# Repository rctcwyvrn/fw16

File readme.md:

# lily's framework 16 modules
Fun little projects

1. An FPGA expansion module
2. A tented, split keyboard on sleds that ride underneath the fw16

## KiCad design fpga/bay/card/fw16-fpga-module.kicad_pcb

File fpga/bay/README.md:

# bay

Expansion Bay work: `KEEPOUT.md` and `POWER.md` (Phase 2 section B), the rear-slot shell modification, and the custom AU15P card KiCad project under `card/` with its `BRINGUP.md`. Community interposer footprints are cloned into `lib/` (git-ignored) and must be pin-checked against the ExpansionBay Electrical README before use.

## FXBeam footprint check (2026-10-28)

Checked by script, pad by pad, against two Framework sources: the pin table in
`ExpansionBay/Electrical/README.md` (pin → signal → column/row) and the Neoconix drawing
`Dual-channel 74P FXBeam, length 27.75mm _Rev 2_` sheet 2, "Recommend DB footprint" (DWG FXBM-X148F027A).
Clones: FrameworkComputer/ExpansionBay `c9b8eef`, XPModder/Framework-ExpansionBay `2ec6368`,
jyancat/ExpansionBay `15efffe`. Framework's README says neither community footprint was tested by them.

Geometry from the drawing (origin at hole E, y up): pads 0.70 × 0.40 mm, column pitch 0.86 mm within a pair,
row pitch 0.60 mm (11 rows A–L, no I); power field on the left, signal field 16.65 mm to its right; columns
numbered 8 → 1 left to right in both fields; signal rows sit 0.25 mm above power rows. Holes: 2 × Ø2.70 NPTH
(interposer screws) with Ø4.50/Ø3.20 SMT rings on the back side, Ø1.50 NPTH × 4 and Ø1.40 NPTH × 2
(alignment). Solder-mask opening ≥ 0.5 × 0.8 mm per pad, i.e. ≥ 0.05 mm mask margin.

| | XPModder `Framework-FX-Beam` | jyancat `Expansion Bay FXBeam` |
| --- | --- | --- |
| Pad numbering | own geometric order (`P-1..74`, `D-1..74`), signal names carried by its symbol | row+column (`PA1`, `SL8`) |
| 148 pad positions | match the drawing | match the drawing |
| Pad → signal | **all 148 match** the README (after name normalisation: `…N`=`…#`, `SDA`=`DAT`) | **PJ6/PJ7/PJ8 are mis-named PJ1/PJ2/PJ3** — as shipped it shorts three GND pads to ID0, Fan1_SPEED and USB+ |
| NPTH diameters | match (drill 1.5 / 1.4 / 2.7; pad sizes 1.6 / 3.2 are mask openings) | match (1.5 / 1.4 / 2.7) |
| SMT rings | present, B.Cu, Ø4.5 pad over the 3.2 hole | **missing** |
| Mask margin | board default (must be ≥ 0.05) | board default (must be ≥ 0.05) |

XPModder's only gap is the mask margin; jyancat's naming bug makes it unsafe. Re-run with `bay/tools/fxbeam_check.py`. Pin-table facts the plan's step-1 list did not have: the power field also carries
**VSYS_GPU ×14** (7–20 V, "up to 10.5 A" on a high-power adapter, 15.2 V min on battery), **PWR_EN** (in, from
the PCH) and **PWR_GOOD** (out, power-sequencing sideband), plus EXT_SSD1/2_RST# and EXT_SSD2_CLK_REQ# for the
second PCIe port; the signal field has TH_OVERT# (PROCHOT#, drive low to throttle the system) and TH_ALERT#.
The "lane crossover" reported by the community was not found in either repo or the README; P/N pad order
does alternate between lanes (e.g. TX0 P below N, TX2 P above N), which is a layout matter, not a swap.

## How the EC powers the bay (research 2026-10-28)

From the FW16 ("lotus") EC source, `FrameworkComputer/EmbeddedController` branch `fwk-lotus-azalea-19573`,
`zephyr/program/framework/lotus/src/{gpu.c,gpu_configuration.c,power_sequence.c,adc.c}`, and
`FrameworkComputer/ExpansionBayConfigurationGenerator`. Not yet verified on hardware.

- **The bay is dead without two things on the card**, 5V_ALW and 3V3_ALW included ("ALW" is a misnomer):
  - ID0 and ID1 must read a valid ADC code (`gpu.c:127-183`): (12,12) = dual-interposer device, ≈2.135 V on
    the EC's 100 k pull-up. Inferred, medium confidence: **330 k to GND on each**, as Input Modules and
    XPModder's design use.
  - An EEPROM descriptor on I2C_*_ALW at 0x50 (or 0x52), magic `32 ac 00 00` + CRC32 + typed blocks
    (PCIE, FAN, VENDOR, GPIO). A blank EEPROM that ACKs falls back to the dual-SSD config. No EEPROM means
    nothing is enabled. XPModder uses a 24LC32.
  - The bay hatch/latch switch must also read closed.
- **The generator's "PCIe accessory" descriptor turns VSYS_GPU on from S3**, 3V/5V from S5, and GPIO0/1_EC high
  from S3. It sets `PCIE_8X1` and PCIE_MUX_SEL high. Write it with `framework_tool` or the EC `gpucfg`
  command. So VSYS_GPU *is* available to a non-GPU card.
- **Suspend:** VSYS stays live in S3/S0ix. The card must drop its own load on PERST# / D3.
- **PWR_EN** is driven by the APU (dGPU BOCO/D3cold) and only watched by the EC. Whether BIOS toggles it
  for an accessory is unknown, so PEX_RST# alone must be enough to gate the link. With PCIE_MUX_SEL high,
  **PWR_GOOD becomes the 2nd CLKREQ# and DP_A_AUX the 2nd REFCLK.**
- **Open:** whether PEX_TX/RX are named from the host or the module side (README marks PEX_TX as a module
  *input*; community thread t/75786 unresolved). Settle it from the GPU board PDFs on ExpansionBay branch
  `gpu_design` before S3. Also open: BIOS bifurcation for the accessory vendor, and Dual M.2 power tree.
  **PEX naming resolved 2026-10-29: host side** — see the next section.

## PEX_TX/RX direction (research 2026-10-29)

**PEX_TX/RX are named from the host side.** PEX_TXn is the laptop's transmitter and enters the card;
PEX_RXn is the card's transmitter. Confidence: medium-high (three independent sources agree, none is a
Framework schematic).

For the fpga sheet and the Path 3 XDC:

| Interposer net | Card end | AC coupling on the card |
| --- | --- | --- |
| PEX_TXn / PEX_TXn# | GTH **RX** (MGTHRXP/N) of lane n | none (the host's TX caps sit on the mainboard) |
| PEX_RXn / PEX_RXn# | GTH **TX** (MGTHTXP/N) of lane n | series cap, placed near the interposer |

Evidence:
- **The GPU board PDFs cannot answer it.** `Graphics Module Reference Design/AMD_7700S_GPU_Board.pdf` and
  `Nvidia_5070_GPU_Board.pdf` (6 sheets each) are mechanical drawings: part list, height zones, outline
  dimensions, FXBeam pad detail (sheet 4, Detail A) and paint lines. They show no components and no net
  names, so AC-cap placement is not visible. `Dual SSD Reference Design/fw_ssd_pcb_ref_design_0.pdf` is
  also mechanical; its sheet 1 has only a pin table.
- **Electrical README I/O column**, which is written from the module's side throughout (VSYS_GPU, Fan*_PWM,
  PWR_EN = I; Fan*_SPEED, PWR_GOOD, PEX_CLK_REQ# = O): PEX_TX0–7 = **I** (signal pins 2–24),
  PEX_RX0–7 = **O** (pins 26–48). The one row that breaks the convention is PEX_REFCLK = O (pins 50/51),
  which must be a typo, since the clock comes from the host.
- **XPModder's IO module** (`XPModder/Framework-ExpansionBay`, `ExpansionBay ExtensionCard
  Module/Framework-ExpansionBay-IO-Module/usb3.kicad_sch`, re-cloned 2026-10-29 at HEAD): PEX_TX0± goes
  straight to the uPD720201's **PERXP/PERXN** (receive, pins 10/11). PEX_RX0± goes through 100 nF caps
  C1/C2 to its transmitter. Traced by wire connectivity, not by eye. Whether that board was built and
  works is unknown.
- **Community thread t/75786 "PCIe data lines":** Filip reports that the M.2 reference board wires interposer
  RX to M.2 RX and TX to TX. M.2 pin names (PETp0 / PERp0) are host-side, so this matches. One community
  report, not from Framework staff.

Consequence: the card puts PCIe Gen4 AC caps (base spec 176–265 nF, i.e. 220 nF 0201/0402) on PEX_RX0–3
only. XPModder's 100 nF suits its Gen2 controller, not Gen4. A TX/RX swap cannot be fixed by lane
polarity inversion, so S3 must keep this mapping.

## Reference PCB vs README (2026-10-28)

`PCB Reference Design/FW_EXPANSION_BAY_PCB_0807.pdf` sheet 2 has its own pin definition table. It agrees with
the Electrical README on every pad except three in the power field: 3PF / 3PG / 2PG are **I2C_CLK_VS /
I2C_DAT_VS / I2C_INT_VS** there, but **EXT_SSD1_RST# / EXT_SSD2_RST# / EXT_SSD2_CLK_REQ#** in the README. The
README is newer (Dual-SSD era), so we follow it; these pads only go to test pads anyway. The same sheet gives
the shell's fan connector: **AFC58-S04FIA-R1 × 2**, pin 1 +12V, 2 FANx_SPEED, 3 FANx_PWM, 4 GND.

## XCAU15P-FFVB676 package facts (2026-10-28)

- **Height:** lidded flip-chip. A (seated, balls included) = 3.12 / 3.31 / 3.52 mm min/nom/max; lid ≤ 22.10 mm
  square on a 27 × 27 mm body; 1.0 mm pitch, 26 × 26. UG575 v1.22 Fig 4-10 (p. 454).
- **Transceivers:** all 12 GTH (Quads 224, 225, 226) sit on the **column 1–7 edge** (the pin-1 side in top
  view): Quad 226 rows F–L, Quad 225 rows M–W, Quad 224 rows Y–AF. UG575 Fig 3-83 (p. 311, top view).
- **PCIe:** a single hard block, PCIE4C_X0Y0 (Gen4 up to x4). Lane-0 quad options per PG213 v1.3 Table 94:
  GTH_Quad_224 (x4), GTH_Quad_225 (x8). REFCLK goes to GTREFCLK0 of the lane-0 quad.

## AFC58-S04FIA-R1 fan connector footprint (research 2026-10-29)

Source: `PCB Reference Design/Datasheets/J200_J201-SP010036Q00_LTCX00A2N00_AFC58-S04FIA-R1.pdf` in the
`gpu_design` clone. Page 1 is the Hefeng customer drawing for the whole AFC58-S series, 0.5 mm pitch,
H = 1.5 mm, FPC/FFC "Easy-on" right-angle SMT, rev A 2020-09-11. Page 2 is the tape and reel. The drawing
is generic, so the CKTS = 4 row of its table applies. Part-number decode (note 4): 04 circuits, **F = lower
contacts**, I = gold flash, A = tape and reel, R1 = natural housing with a black latch. A web search on
2026-10-29 found no LCSC/JLCPCB listing under this number (LCSC itself not queried directly), so plan for
consignment or hand placement.

**Verify before creating the footprint.** The page is a raster image. It could only be read at thumbnail
resolution here, because `pdftoppm`, `pdftocairo` and `pdfimages` needed approval that a headless run
could not get. Rows marked **(low-res)** need a check against a zoomed render.

| Item | Value | Drawing callout |
| --- | --- | --- |
| Signal pads | 4, numbered 1–4 from the "Circuit 1" end | "Recommended P.C.B pattern layout" |
| Pad pitch | 0.50 ± 0.05 mm | pattern, top-left |
| Signal pad width | 0.30 ± 0.05 mm | pattern, top-right |
| Signal pad length | 1.10 ± 0.05 mm **(low-res)** | pattern, right vertical callout |
| Pad 1 → pad 4 centre span | DIM A = 1.50 ± 0.05 mm | pattern "DIM A", table CKTS 4 |
| Fitting-nail pads | 2, mechanical (unnumbered, or "MP") | pattern, both ends |
| Nail pad size | 1.00 ± 0.05 (X) × 1.60 ± 0.05 (Y) mm **(low-res)** | pattern, bottom-left |
| Nail pad inner edge → pad 1 centre (X) | 1.60 ± 0.05 mm **(low-res)**. Working reading: nail centres at X = ±2.85 mm from the connector centre, giving an outer copper span of 6.70 mm. | pattern, bottom "1.60 ± 0.05". The "(0.15)" reference by Circuit 1 suggests the callout ends on the pad centreline. |
| Signal row → nail pads (Y) | 2.00 ± 0.05 mm **(low-res)**. Unclear whether it runs from the signal-pad outer edge to the nail-pad near edge or to the far edge. | pattern, right "2.00 ± 0.05" |
| Housing width | DIM A + 2.56 = 4.06 mm | top view |
| Overall width incl. nails | DIM B = 6.40 ± 0.15 mm | front view, table |
| DIM C / DIM D | 2.60 ± 0.05 / 5.40 ± 0.10 mm | front view, table |
| Depth | 3.83 mm body; 4.45 mm overall; terminal tail 1.10 mm | side view |
| Height | 1.50 mm (datum Z); latch opens to 105° | side view, section A-A |
| Mating FPC | 0.30 ± 0.03 mm thick, 2.50 ± 0.08 mm wide (DIM A + 1.00), conductors 0.30 ± 0.03 mm on 0.50 pitch, ≥ 2.70 mm exposed, ≥ 3.5 mm stiffener | "Recommended FPC/FFC dimension" |

Sanity check: the 6.70 mm working-reading pad span is wider than the 6.40 mm part (nail pads overhanging the
nails), which is how such land patterns usually look. The other reading, 1.60 mm nail-centre to pad-1-centre,
gives a 5.70 mm span, narrower than the part, which is unlikely. Pinout (FW_EXPANSION_BAY_PCB_0807.pdf
sheet 2): 1 +12V_FAN, 2 FANx_SPEED, 3 FANx_PWM, 4 GND. **Open:** which side of the fan FPC has its contacts
exposed. A lower-contact connector needs the conductors facing the board. The UMA fan spec PDFs have no
extractable text.

**Verified 2026-10-29 against a 300 dpi render, and built as `fw16-fpga-module:AFC58-S04FIA-R1`.** The low-res rows hold.
The 2.00 mm callout runs from the signal-pad edge nearest the nails to the far edge of the nail pad. The
top view's 3.10 mm (terminal tip to the nail edge) equals 1.10 + 2.00, and the nail metal sits 1.93–3.10 mm behind
the terminal tip. The pad-1 centre is 1.60 mm from the nail pad's inner edge.

Footprint frame: origin at the signal-pad centre. Pads 1–4 are 0.30 × 1.10 mm at x = −0.75…+0.75, y = 0. The two `MP`
nail pads are 1.00 × 1.60 mm at x = ±2.85, y = +1.75. The terminal tip is at y −0.70, and the housing runs to y +3.75.
The courtyard is ±3.6 × (−0.95…+4.0). The MP pads have no net, because the symbol is a plain `Conn_01x04`. Tie them
to GND in the PCB if the reference board does. The connectors go on the **bottom** side (CAD), so flip them at
placement.

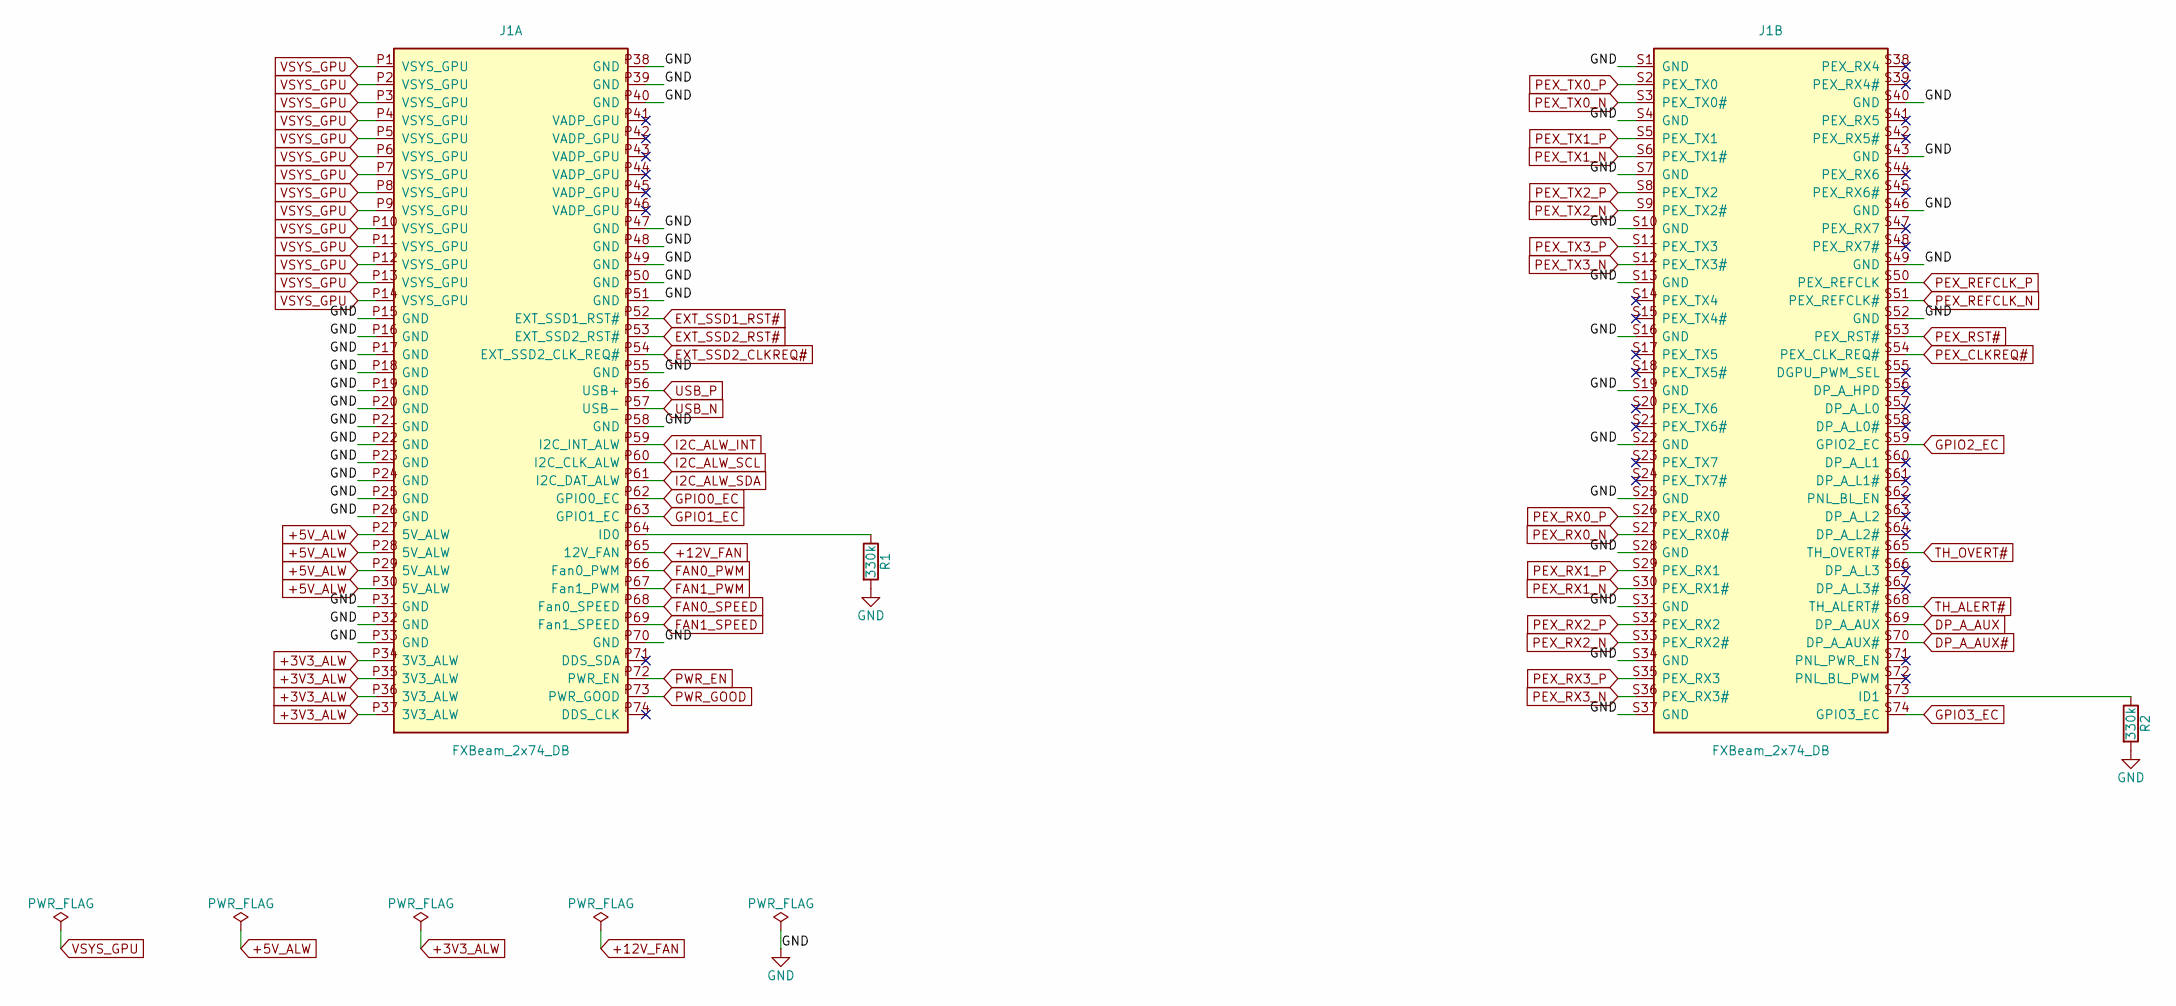
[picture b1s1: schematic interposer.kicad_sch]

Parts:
J1: FXBeam_2x74_DB
R1, R2: 330k; R_0402_1005Metric

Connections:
+3V3_ALW: J1.P34 (3V3_ALW), J1.P35 (3V3_ALW), J1.P36 (3V3_ALW), J1.P37 (3V3_ALW); also elsewhere on the board
+5V_ALW: J1.P27 (5V_ALW), J1.P28 (5V_ALW), J1.P29 (5V_ALW), J1.P30 (5V_ALW); also elsewhere on the board
+12V_FAN: J1.P65 (12V_FAN); also elsewhere on the board
DP_A_AUX: J1.S69 (DP_A_AUX); also elsewhere on the board
DP_A_AUX#: J1.S70 (DP_A_AUX#); also elsewhere on the board
EXT_SSD1_RST#: J1.P52 (EXT_SSD1_RST#); also elsewhere on the board
EXT_SSD2_CLKREQ#: J1.P54 (EXT_SSD2_CLK_REQ#); also elsewhere on the board
EXT_SSD2_RST#: J1.P53 (EXT_SSD2_RST#); also elsewhere on the board
FAN0_PWM: J1.P66 (Fan0_PWM); also elsewhere on the board
FAN0_SPEED: J1.P68 (Fan0_SPEED); also elsewhere on the board
FAN1_PWM: J1.P67 (Fan1_PWM); also elsewhere on the board
FAN1_SPEED: J1.P69 (Fan1_SPEED); also elsewhere on the board
GND: J1.P15 (GND), J1.P16 (GND), J1.P17 (GND), J1.P18 (GND), J1.P19 (GND), J1.P20 (GND), J1.P21 (GND), J1.P22 (GND), J1.P23 (GND), J1.P24 (GND), J1.P25 (GND), J1.P26 (GND), J1.P31 (GND), J1.P32 (GND), J1.P33 (GND), J1.P38 (GND), J1.P39 (GND), J1.P40 (GND), J1.P47 (GND), J1.P48 (GND), J1.P49 (GND), J1.P50 (GND), J1.P51 (GND), J1.P55 (GND), J1.P58 (GND), J1.P70 (GND), J1.S1 (GND), J1.S4 (GND), J1.S7 (GND), J1.S10 (GND), J1.S13 (GND), J1.S16 (GND), J1.S19 (GND), J1.S22 (GND), J1.S25 (GND), J1.S28 (GND), J1.S31 (GND), J1.S34 (GND), J1.S37 (GND), J1.S40 (GND), J1.S43 (GND), J1.S46 (GND), J1.S49 (GND), J1.S52 (GND), R1.2, R2.2; also elsewhere on the board
GPIO0_EC: J1.P62 (GPIO0_EC); also elsewhere on the board
GPIO1_EC: J1.P63 (GPIO1_EC); also elsewhere on the board
GPIO2_EC: J1.S59 (GPIO2_EC); also elsewhere on the board
GPIO3_EC: J1.S74 (GPIO3_EC); also elsewhere on the board
I2C_ALW_INT: J1.P59 (I2C_INT_ALW); also elsewhere on the board
I2C_ALW_SCL: J1.P60 (I2C_CLK_ALW); also elsewhere on the board
I2C_ALW_SDA: J1.P61 (I2C_DAT_ALW); also elsewhere on the board
unnamed: J1.P64 (ID0), R1.1
unnamed: J1.S73 (ID1), R2.1
PEX_CLKREQ#: J1.S54 (PEX_CLK_REQ#); also elsewhere on the board
PEX_REFCLK_N: J1.S51 (PEX_REFCLK#); also elsewhere on the board
PEX_REFCLK_P: J1.S50 (PEX_REFCLK); also elsewhere on the board
PEX_RST#: J1.S53 (PEX_RST#); also elsewhere on the board
PEX_RX0_N: J1.S27 (PEX_RX0#); also elsewhere on the board
PEX_RX0_P: J1.S26 (PEX_RX0); also elsewhere on the board
PEX_RX1_N: J1.S30 (PEX_RX1#); also elsewhere on the board
PEX_RX1_P: J1.S29 (PEX_RX1); also elsewhere on the board
PEX_RX2_N: J1.S33 (PEX_RX2#); also elsewhere on the board
PEX_RX2_P: J1.S32 (PEX_RX2); also elsewhere on the board
PEX_RX3_N: J1.S36 (PEX_RX3#); also elsewhere on the board
PEX_RX3_P: J1.S35 (PEX_RX3); also elsewhere on the board
PEX_TX0_N: J1.S3 (PEX_TX0#); also elsewhere on the board
PEX_TX0_P: J1.S2 (PEX_TX0); also elsewhere on the board
PEX_TX1_N: J1.S6 (PEX_TX1#); also elsewhere on the board
PEX_TX1_P: J1.S5 (PEX_TX1); also elsewhere on the board
PEX_TX2_N: J1.S9 (PEX_TX2#); also elsewhere on the board
PEX_TX2_P: J1.S8 (PEX_TX2); also elsewhere on the board
PEX_TX3_N: J1.S12 (PEX_TX3#); also elsewhere on the board
PEX_TX3_P: J1.S11 (PEX_TX3); also elsewhere on the board
PWR_EN: J1.P72 (PWR_EN); also elsewhere on the board
PWR_GOOD: J1.P73 (PWR_GOOD); also elsewhere on the board
TH_ALERT#: J1.S68 (TH_ALERT#); also elsewhere on the board
TH_OVERT#: J1.S65 (TH_OVERT#); also elsewhere on the board
USB_N: J1.P57 (USB-); also elsewhere on the board
USB_P: J1.P56 (USB+); also elsewhere on the board
VSYS_GPU: J1.P1 (VSYS_GPU), J1.P2 (VSYS_GPU), J1.P3 (VSYS_GPU), J1.P4 (VSYS_GPU), J1.P5 (VSYS_GPU), J1.P6 (VSYS_GPU), J1.P7 (VSYS_GPU), J1.P8 (VSYS_GPU), J1.P9 (VSYS_GPU), J1.P10 (VSYS_GPU), J1.P11 (VSYS_GPU), J1.P12 (VSYS_GPU), J1.P13 (VSYS_GPU), J1.P14 (VSYS_GPU); also elsewhere on the board

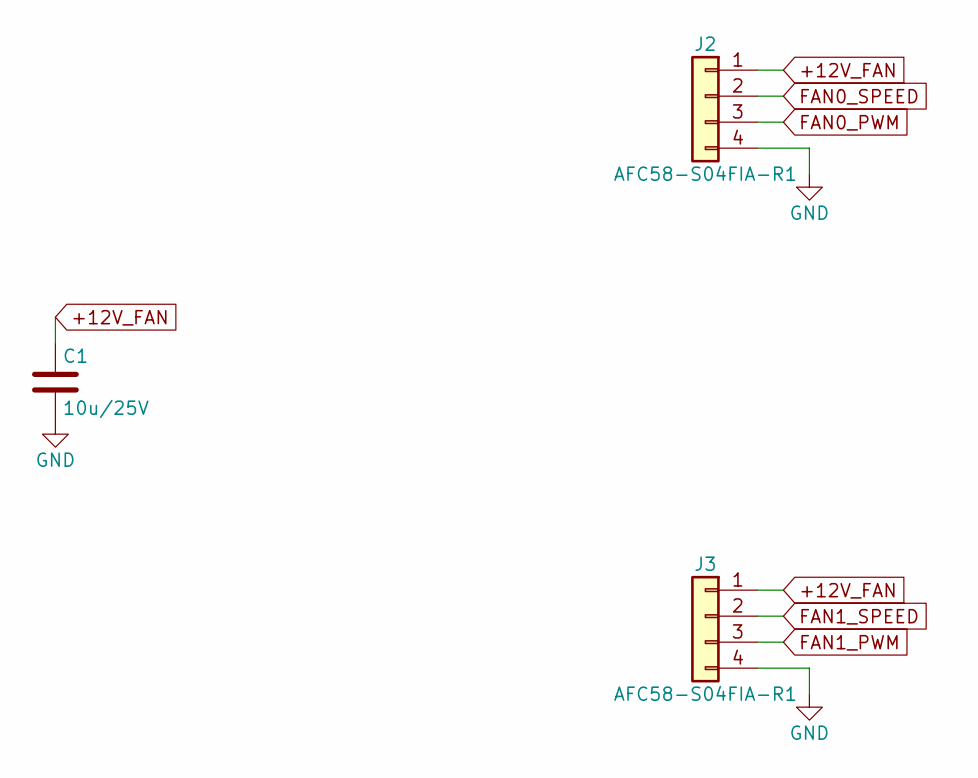
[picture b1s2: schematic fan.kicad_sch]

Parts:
C1: 10u/25V; C_1206_3216Metric
J2, J3: AFC58-S04FIA-R1

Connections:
+12V_FAN: C1.1, J2.1, J3.1; also elsewhere on the board
FAN0_PWM: J2.3; also elsewhere on the board
FAN0_SPEED: J2.2; also elsewhere on the board
FAN1_PWM: J3.3; also elsewhere on the board
FAN1_SPEED: J3.2; also elsewhere on the board
GND: C1.2, J2.4, J3.4; also elsewhere on the board

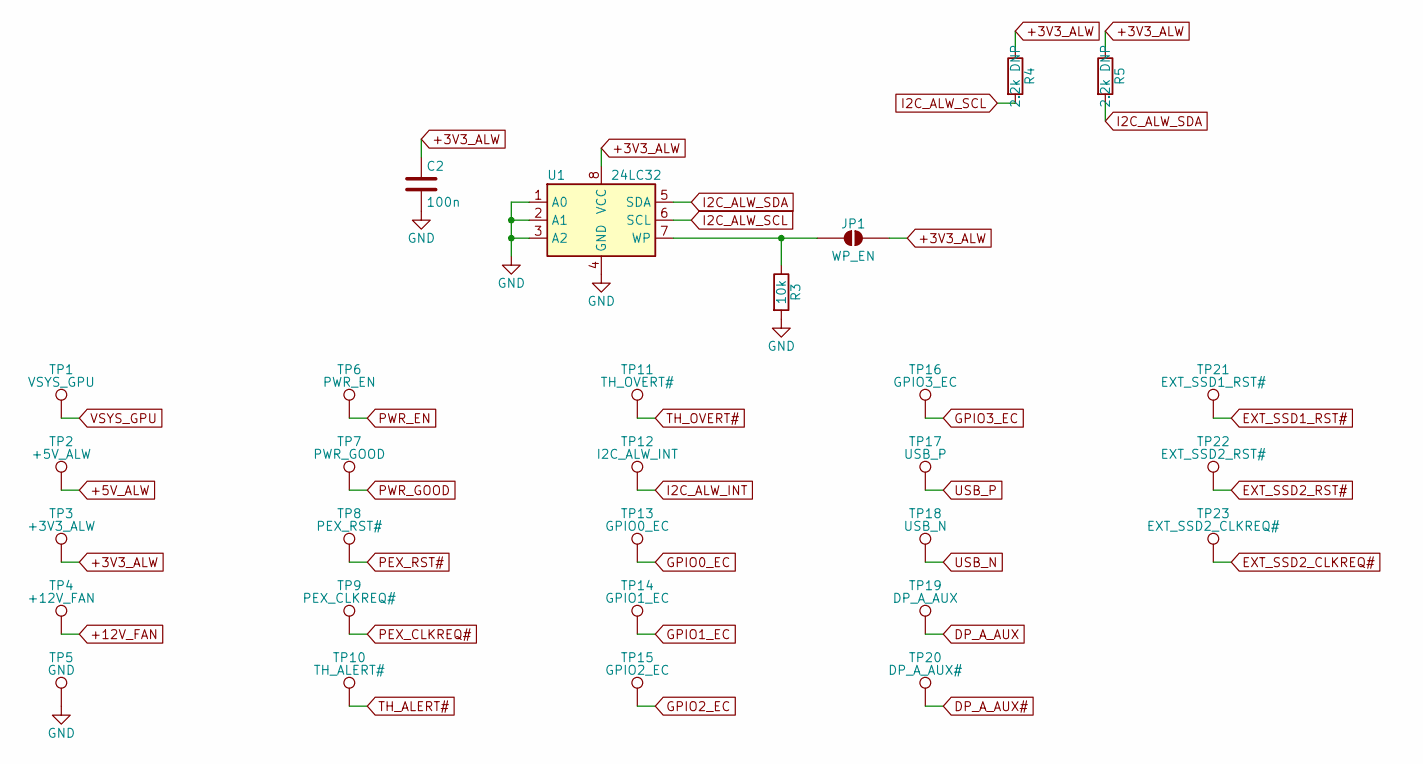
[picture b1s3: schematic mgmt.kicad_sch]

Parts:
C2: 100n; C_0402_1005Metric
JP1: WP_EN; SolderJumper-2_P1.3mm_Open_Pad1.0x1.5mm
R3: 10k; R_0402_1005Metric
R4, R5: 2.2k DNP; R_0402_1005Metric
TP1: VSYS_GPU; TestPoint_Pad_D1.0mm
TP2: +5V_ALW; TestPoint_Pad_D1.0mm
TP3: +3V3_ALW; TestPoint_Pad_D1.0mm
TP4: +12V_FAN; TestPoint_Pad_D1.0mm
TP5: GND; TestPoint_Pad_D1.0mm
TP6: PWR_EN; TestPoint_Pad_D1.0mm
TP7: PWR_GOOD; TestPoint_Pad_D1.0mm
TP8: PEX_RST#; TestPoint_Pad_D1.0mm
TP9: PEX_CLKREQ#; TestPoint_Pad_D1.0mm
TP10: TH_ALERT#; TestPoint_Pad_D1.0mm
TP11: TH_OVERT#; TestPoint_Pad_D1.0mm
TP12: I2C_ALW_INT; TestPoint_Pad_D1.0mm
TP13: GPIO0_EC; TestPoint_Pad_D1.0mm
TP14: GPIO1_EC; TestPoint_Pad_D1.0mm
TP15: GPIO2_EC; TestPoint_Pad_D1.0mm
TP16: GPIO3_EC; TestPoint_Pad_D1.0mm
TP17: USB_P; TestPoint_Pad_D1.0mm
TP18: USB_N; TestPoint_Pad_D1.0mm
TP19: DP_A_AUX; TestPoint_Pad_D1.0mm
TP20: DP_A_AUX#; TestPoint_Pad_D1.0mm
TP21: EXT_SSD1_RST#; TestPoint_Pad_D1.0mm
TP22: EXT_SSD2_RST#; TestPoint_Pad_D1.0mm
TP23: EXT_SSD2_CLKREQ#; TestPoint_Pad_D1.0mm
U1: 24LC32; TSSOP-8_4.4x3mm_P0.65mm

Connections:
+3V3_ALW: C2.1, JP1.2 (B), R4.1, R5.1, TP3.1, U1.8 (VCC); also elsewhere on the board
+5V_ALW: TP2.1; also elsewhere on the board
+12V_FAN: TP4.1; also elsewhere on the board
DP_A_AUX: TP19.1; also elsewhere on the board
DP_A_AUX#: TP20.1; also elsewhere on the board
EXT_SSD1_RST#: TP21.1; also elsewhere on the board
EXT_SSD2_CLKREQ#: TP23.1; also elsewhere on the board
EXT_SSD2_RST#: TP22.1; also elsewhere on the board
GND: C2.2, R3.2, TP5.1, U1.1 (A0), U1.2 (A1), U1.3 (A2), U1.4 (GND); also elsewhere on the board
GPIO0_EC: TP13.1; also elsewhere on the board
GPIO1_EC: TP14.1; also elsewhere on the board
GPIO2_EC: TP15.1; also elsewhere on the board
GPIO3_EC: TP16.1; also elsewhere on the board
I2C_ALW_INT: TP12.1; also elsewhere on the board
I2C_ALW_SCL: R4.2, U1.6 (SCL); also elsewhere on the board
I2C_ALW_SDA: R5.2, U1.5 (SDA); also elsewhere on the board
unnamed: JP1.1 (A), R3.1, U1.7 (WP)
PEX_CLKREQ#: TP9.1; also elsewhere on the board
PEX_RST#: TP8.1; also elsewhere on the board
PWR_EN: TP6.1; also elsewhere on the board
PWR_GOOD: TP7.1; also elsewhere on the board
TH_ALERT#: TP10.1; also elsewhere on the board
TH_OVERT#: TP11.1; also elsewhere on the board
USB_N: TP18.1; also elsewhere on the board
USB_P: TP17.1; also elsewhere on the board
VSYS_GPU: TP1.1; also elsewhere on the board

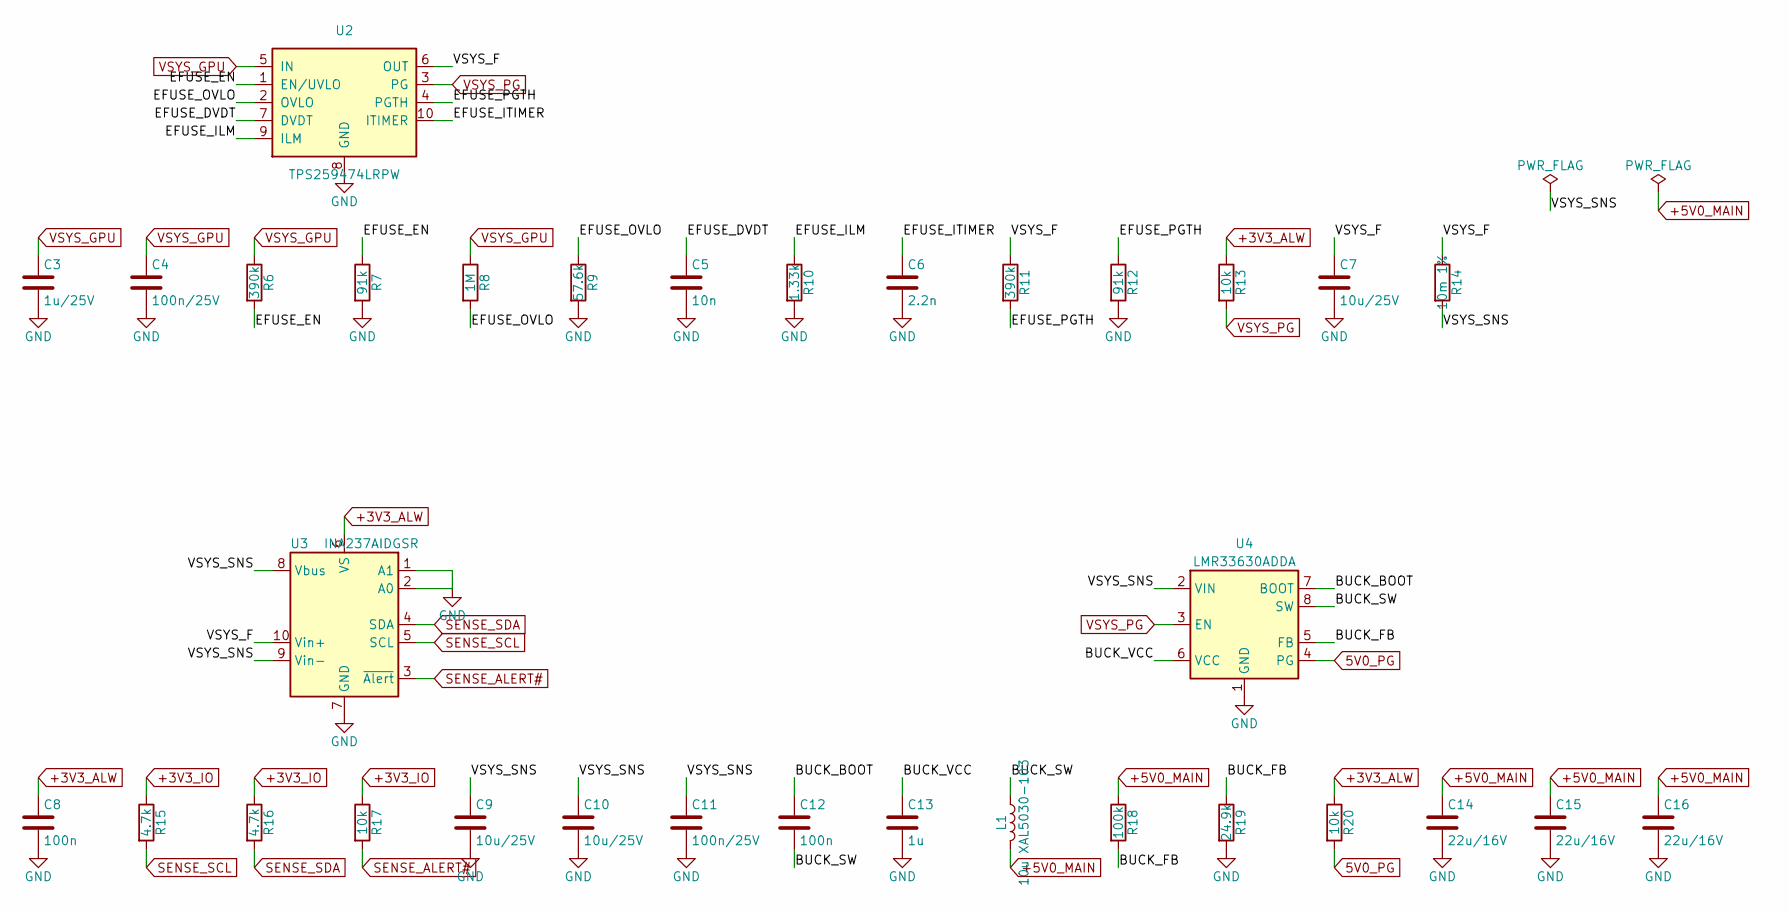
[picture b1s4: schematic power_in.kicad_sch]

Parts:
C3: 1u/25V; C_0603_1608Metric
C4, C11: 100n/25V; C_0402_1005Metric
C5: 10n; C_0402_1005Metric
C6: 2.2n; C_0402_1005Metric
C7, C9, C10: 10u/25V; C_1206_3216Metric
C8, C12: 100n; C_0402_1005Metric
C13: 1u; C_0402_1005Metric
C14, C15, C16: 22u/16V; C_1206_3216Metric
L1: 10u XAL5030-103; L_Coilcraft_XAL5030-XXX
R6, R11: 390k; R_0402_1005Metric
R7, R12: 91k; R_0402_1005Metric
R8: 1M; R_0402_1005Metric
R9: 57.6k; R_0402_1005Metric
R10: 1.33k; R_0402_1005Metric
R13, R17, R20: 10k; R_0402_1005Metric
R14: 10m 1%; R_1206_3216Metric
R15, R16: 4.7k; R_0402_1005Metric
R18: 100k; R_0402_1005Metric
R19: 24.9k; R_0402_1005Metric
U2: TPS259474LRPW; Texas_RPW0010A_VQFN-HR-10_2x2mm
U3: INA237AIDGSR; TSSOP-10_3x3mm_P0.5mm
U4: LMR33630ADDA; Texas_HSOP-8-1EP_3.9x4.9mm_P1.27mm_ThermalVias

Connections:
5V0_PG: R20.2, U4.4 (PG); also elsewhere on the board
+3V3_ALW: C8.1, R13.1, R20.1, U3.6 (VS); also elsewhere on the board
+3V3_IO: R15.1, R16.1, R17.1; also elsewhere on the board
+5V0_MAIN: C14.1, C15.1, C16.1, L1.2, R18.1; also elsewhere on the board
/Power input/BUCK_BOOT: C12.1, U4.7 (BOOT)
/Power input/BUCK_FB: R18.2, R19.1, U4.5 (FB)
/Power input/BUCK_SW: C12.2, L1.1, U4.8 (SW)
/Power input/BUCK_VCC: C13.1, U4.6 (VCC)
/Power input/EFUSE_DVDT: C5.1, U2.7 (DVDT)
/Power input/EFUSE_EN: R6.2, R7.1, U2.1 (EN/UVLO)
/Power input/EFUSE_ILM: R10.1, U2.9 (ILM)
/Power input/EFUSE_ITIMER: C6.1, U2.10 (ITIMER)
/Power input/EFUSE_OVLO: R8.2, R9.1, U2.2 (OVLO)
/Power input/EFUSE_PGTH: R11.2, R12.1, U2.4 (PGTH)
/Power input/VSYS_F: C7.1, R11.1, R14.1, U2.6 (OUT), U3.10 (Vin+)
/Power input/VSYS_SNS: C9.1, C10.1, C11.1, R14.2, U3.8 (Vbus), U3.9 (Vin-), U4.2 (VIN)
GND: C3.2, C4.2, C5.2, C6.2, C7.2, C8.2, C9.2, C10.2, C11.2, C13.2, C14.2, C15.2, C16.2, R7.2, R9.2, R10.2, R12.2, R19.2, U2.8 (GND), U3.1 (A1), U3.2 (A0), U3.7 (GND), U4.1 (GND), U4.9 (GND); also elsewhere on the board
SENSE_ALERT#: R17.2, U3.3 (~Alert); also elsewhere on the board
SENSE_SCL: R15.2, U3.5 (SCL); also elsewhere on the board
SENSE_SDA: R16.2, U3.4 (SDA); also elsewhere on the board
VSYS_GPU: C3.1, C4.1, R6.1, R8.1, U2.5 (IN); also elsewhere on the board
VSYS_PG: R13.2, U2.3 (PG), U4.3 (EN)

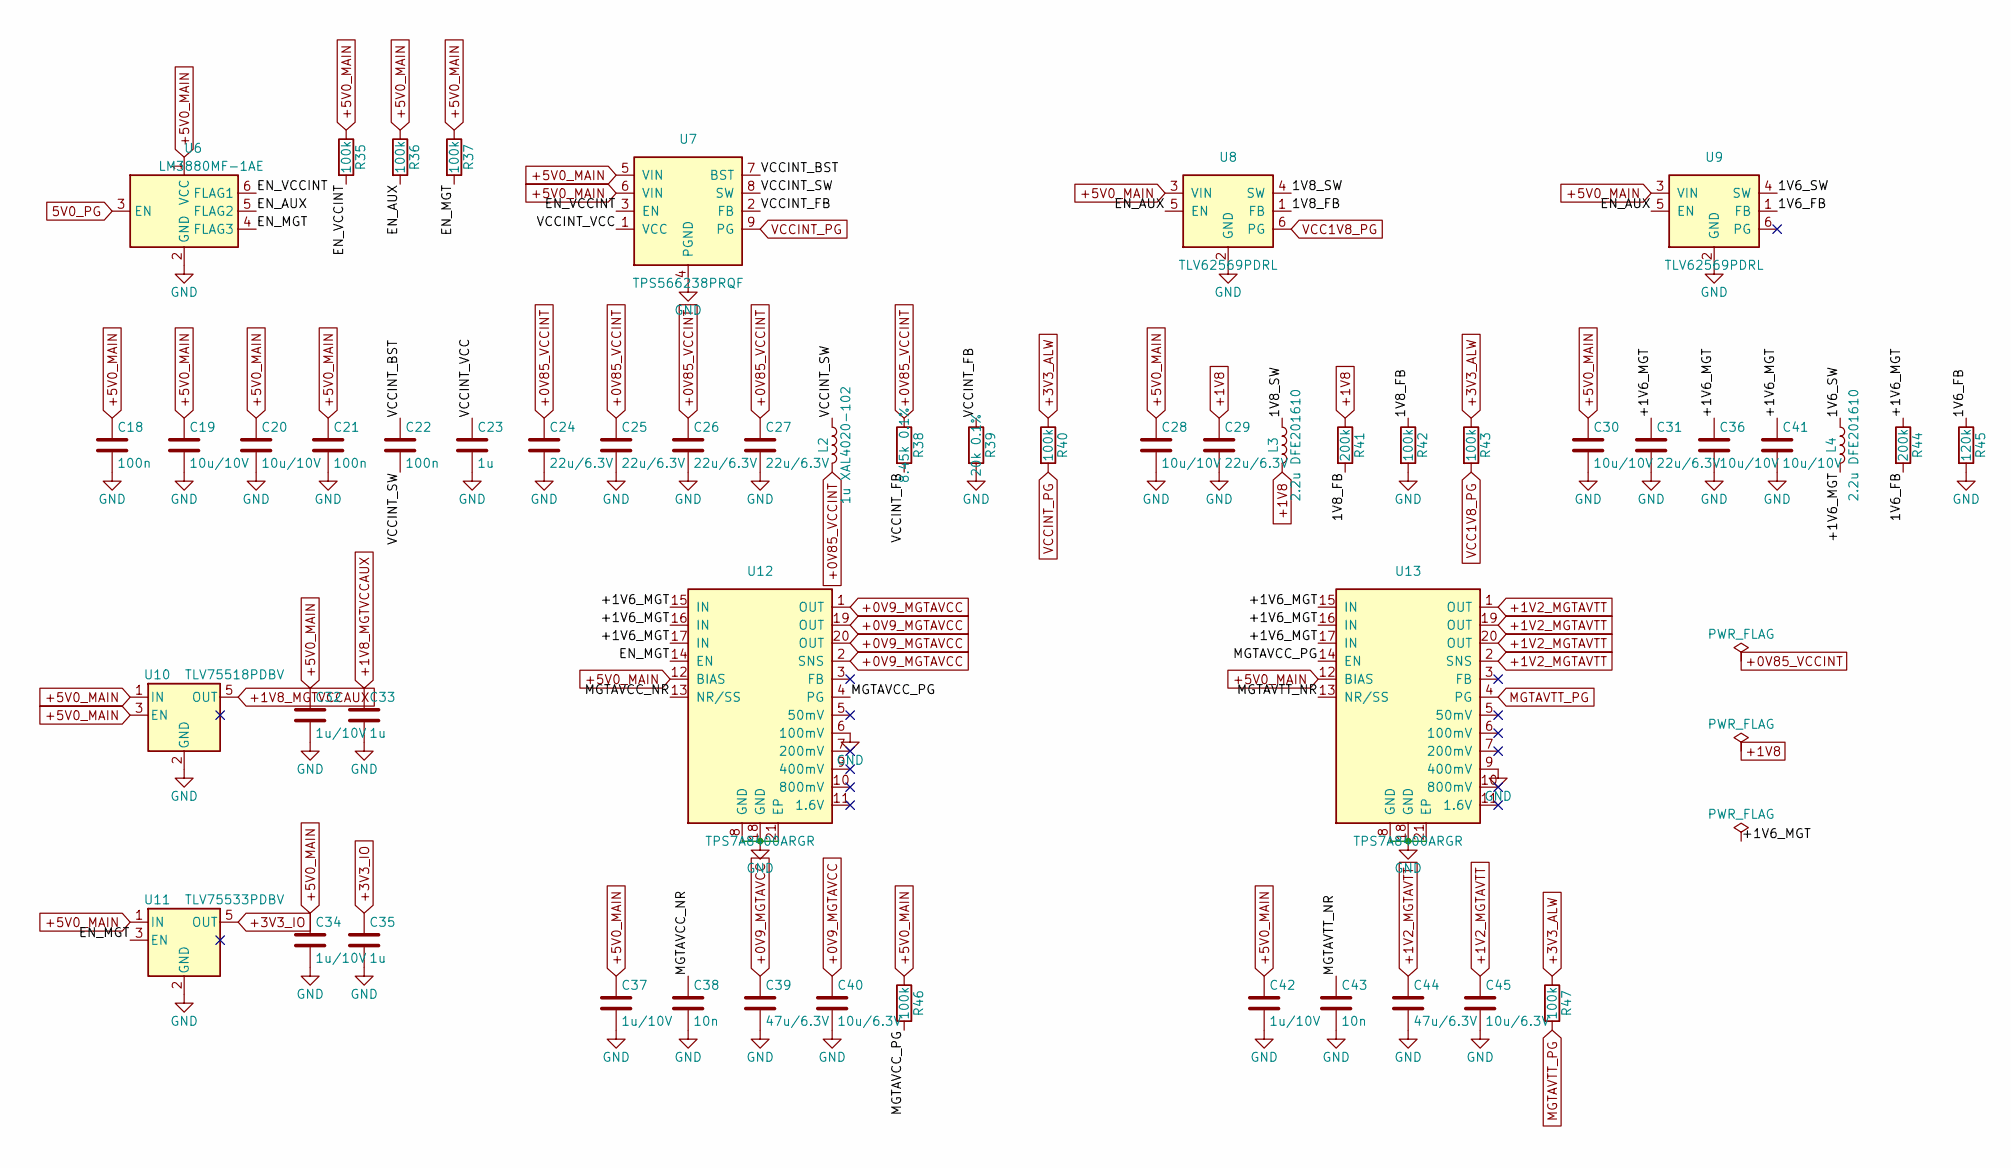
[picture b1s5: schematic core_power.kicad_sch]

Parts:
C18, C21, C22: 100n; C_0402_1005Metric
C19, C20, C28, C30, C36, C41: 10u/10V; C_0805_2012Metric
C23, C33, C35: 1u; C_0402_1005Metric
C24, C25, C26, C27, C29, C31: 22u/6.3V; C_0805_2012Metric
C32, C34, C37, C42: 1u/10V; C_0402_1005Metric
C38, C43: 10n; C_0402_1005Metric
C39, C44: 47u/6.3V; C_1206_3216Metric
C40, C45: 10u/6.3V; C_0805_2012Metric
L2: 1u XAL4020-102; L_Coilcraft_XAL4020-XXX
L3, L4: 2.2u DFE201610; L_Murata_DFE201610P
R35, R36, R37, R40, R42, R43, R46, R47: 100k; R_0402_1005Metric
R38: 8.45k 0.1%; R_0402_1005Metric
R39: 20k 0.1%; R_0402_1005Metric
R41, R44: 200k; R_0402_1005Metric
R45: 120k; R_0402_1005Metric
U6: LM3880MF-1AE; SOT-23-6
U7: TPS566238PRQF; Texas_RQF0009A_VQFN-HR-9_1.5x2mm
U8, U9: TLV62569PDRL; SOT-563
U10: TLV75518PDBV; SOT-23-5
U11: TLV75533PDBV; SOT-23-5
U12, U13: TPS7A8400ARGR; QFN-20-1EP_3.5x3.5mm_P0.5mm_EP2x2mm_ThermalVias

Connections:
5V0_PG: U6.3 (EN); also elsewhere on the board
+0V9_MGTAVCC: C39.1, C40.1, U12.1 (OUT), U12.2 (SNS), U12.19 (OUT), U12.20 (OUT); also elsewhere on the board
+0V85_VCCINT: C24.1, C25.1, C26.1, C27.1, L2.2, R38.1; also elsewhere on the board
+1V2_MGTAVTT: C44.1, C45.1, U13.1 (OUT), U13.2 (SNS), U13.19 (OUT), U13.20 (OUT); also elsewhere on the board
+1V8: C29.1, L3.2, R41.1; also elsewhere on the board
+1V8_MGTVCCAUX: C33.1, U10.5 (OUT); also elsewhere on the board
+3V3_ALW: R40.1, R43.1, R47.1; also elsewhere on the board
+3V3_IO: C35.1, U11.5 (OUT); also elsewhere on the board
+5V0_MAIN: C18.1, C19.1, C20.1, C21.1, C28.1, C30.1, C32.1, C34.1, C37.1, C42.1, R35.1, R36.1, R37.1, R46.1, U6.1 (VCC), U7.5 (VIN), U7.6 (VIN), U8.3 (VIN), U9.3 (VIN), U10.1 (IN), U10.3 (EN), U11.1 (IN), U12.12 (BIAS), U13.12 (BIAS); also elsewhere on the board
/Core power/1V6_FB: R44.2, R45.1, U9.1 (FB)
/Core power/1V6_SW: L4.1, U9.4 (SW)
/Core power/1V8_FB: R41.2, R42.1, U8.1 (FB)
/Core power/1V8_SW: L3.1, U8.4 (SW)
/Core power/+1V6_MGT: C31.1, C36.1, C41.1, L4.2, R44.1, U12.15 (IN), U12.16 (IN), U12.17 (IN), U13.15 (IN), U13.16 (IN), U13.17 (IN)
/Core power/EN_AUX: R36.2, U6.5 (FLAG2), U8.5 (EN), U9.5 (EN)
/Core power/EN_MGT: R37.2, U6.4 (FLAG3), U11.3 (EN), U12.14 (EN)
/Core power/EN_VCCINT: R35.2, U6.6 (FLAG1), U7.3 (EN)
/Core power/MGTAVCC_NR: C38.1, U12.13 (NR/SS)
/Core power/MGTAVCC_PG: R46.2, U12.4 (PG), U13.14 (EN)
/Core power/MGTAVTT_NR: C43.1, U13.13 (NR/SS)
/Core power/VCCINT_BST: C22.1, U7.7 (BST)
/Core power/VCCINT_FB: R38.2, R39.1, U7.2 (FB)
/Core power/VCCINT_SW: C22.2, L2.1, U7.8 (SW)
/Core power/VCCINT_VCC: C23.1, U7.1 (VCC)
GND: C18.2, C19.2, C20.2, C21.2, C23.2, C24.2, C25.2, C26.2, C27.2, C28.2, C29.2, C30.2, C31.2, C32.2, C33.2, C34.2, C35.2, C36.2, C37.2, C38.2, C39.2, C40.2, C41.2, C42.2, C43.2, C44.2, C45.2, R39.2, R42.2, R45.2, U6.2 (GND), U7.4 (PGND), U8.2 (GND), U9.2 (GND), U10.2 (GND), U11.2 (GND), U12.6 (100mV), U12.8 (GND), U12.18 (GND), U12.21 (EP), U13.8 (GND), U13.9 (400mV), U13.18 (GND), U13.21 (EP); also elsewhere on the board
MGTAVTT_PG: R47.2, U13.4 (PG)
VCC1V8_PG: R43.2, U8.6 (PG)
VCCINT_PG: R40.2, U7.9 (PG)

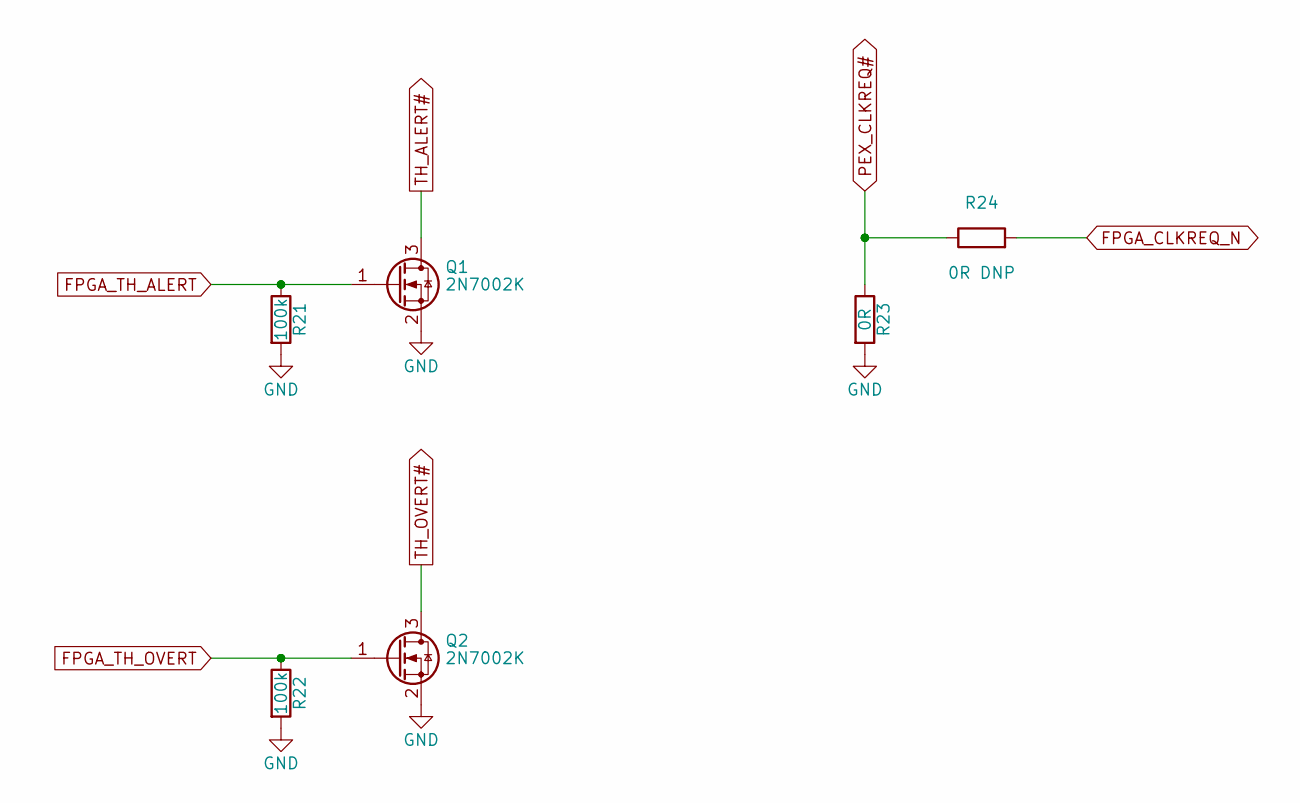
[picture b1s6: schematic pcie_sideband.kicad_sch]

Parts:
Q1, Q2: 2N7002K; SOT-23
R21, R22: 100k; R_0402_1005Metric
R23: 0R; R_0402_1005Metric
R24: 0R DNP; R_0402_1005Metric

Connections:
FPGA_CLKREQ_N: R24.2; also elsewhere on the board
FPGA_TH_ALERT: Q1.1 (G), R21.1; also elsewhere on the board
FPGA_TH_OVERT: Q2.1 (G), R22.1; also elsewhere on the board
GND: Q1.2 (S), Q2.2 (S), R21.2, R22.2, R23.2; also elsewhere on the board
PEX_CLKREQ#: R23.1, R24.1; also elsewhere on the board
TH_ALERT#: Q1.3 (D); also elsewhere on the board
TH_OVERT#: Q2.3 (D); also elsewhere on the board

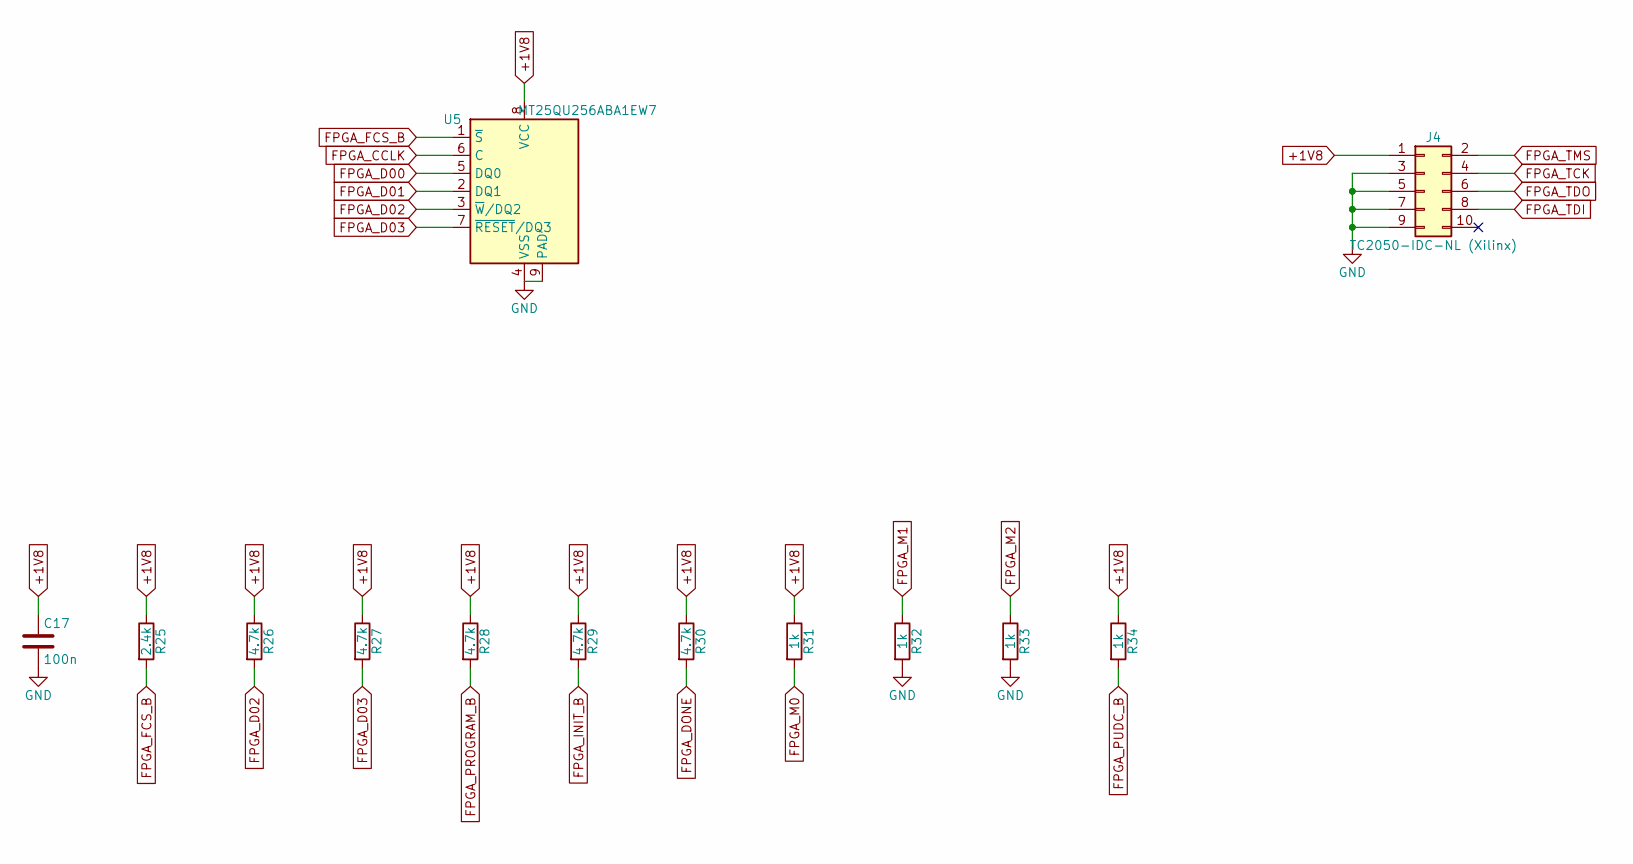
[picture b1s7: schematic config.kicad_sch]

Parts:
C17: 100n; C_0402_1005Metric
J4: TC2050-IDC-NL (Xilinx); Tag-Connect_TC2050-IDC-NL_2x05_P1.27mm_Vertical
R25: 2.4k; R_0402_1005Metric
R26, R27, R28, R29, R30: 4.7k; R_0402_1005Metric
R31, R32, R33, R34: 1k; R_0402_1005Metric
U5: MT25QU256ABA1EW7; W-PDFN-8-1EP_6x5mm_P1.27mm_EP3x3mm

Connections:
+1V8: C17.1, J4.1, R25.1, R26.1, R27.1, R28.1, R29.1, R30.1, R31.1, R34.1, U5.8 (VCC); also elsewhere on the board
FPGA_CCLK: U5.6 (C); also elsewhere on the board
FPGA_D00: U5.5 (DQ0); also elsewhere on the board
FPGA_D01: U5.2 (DQ1); also elsewhere on the board
FPGA_D02: R26.2, U5.3 (~W/DQ2); also elsewhere on the board
FPGA_D03: R27.2, U5.7 (~RESET/DQ3); also elsewhere on the board
FPGA_DONE: R30.2; also elsewhere on the board
FPGA_FCS_B: R25.2, U5.1 (~S); also elsewhere on the board
FPGA_INIT_B: R29.2; also elsewhere on the board
FPGA_M0: R31.2; also elsewhere on the board
FPGA_M1: R32.1; also elsewhere on the board
FPGA_M2: R33.1; also elsewhere on the board
FPGA_PROGRAM_B: R28.2; also elsewhere on the board
FPGA_PUDC_B: R34.2; also elsewhere on the board
FPGA_TCK: J4.4; also elsewhere on the board
FPGA_TDI: J4.8; also elsewhere on the board
FPGA_TDO: J4.6; also elsewhere on the board
FPGA_TMS: J4.2; also elsewhere on the board
GND: C17.2, J4.3, J4.5, J4.7, J4.9, R32.2, R33.2, U5.4 (VSS), U5.9 (PAD); also elsewhere on the board
